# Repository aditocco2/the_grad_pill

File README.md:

# Overblinking: The LED Matrix Graduation Cap

A DIY graduation cap project that shows a slideshow of pictures, GIFs, videos, and scrolling text messages on a 64x64 LED matrix.

Includes a high-performance LED matrix driver, a custom 3D printed mounting system, and a custom PCB.

## Features
- Easy loading of data onto the SD card - no manual downscaling or image dumping needed
- SD card is exposed underneath the cap with a custom PCB, allowing easy replacement of cards
- Mode switch allows you to automatically switch to a less distracting "static mode" during speeches
- Whole system is powered through one battery pack
- Optional rain resistance using an acrylic sheet and 3D printed waterproofing shield
- Automatically initializes/recovers SD cards and survives card swaps
- Only required electronics skill for assembly is through-hole soldering

## Build Your Own
For instructions on how to make your own LED matrix graduation cap, read the full guide [here](https://overblinking.substack.com/guide)!

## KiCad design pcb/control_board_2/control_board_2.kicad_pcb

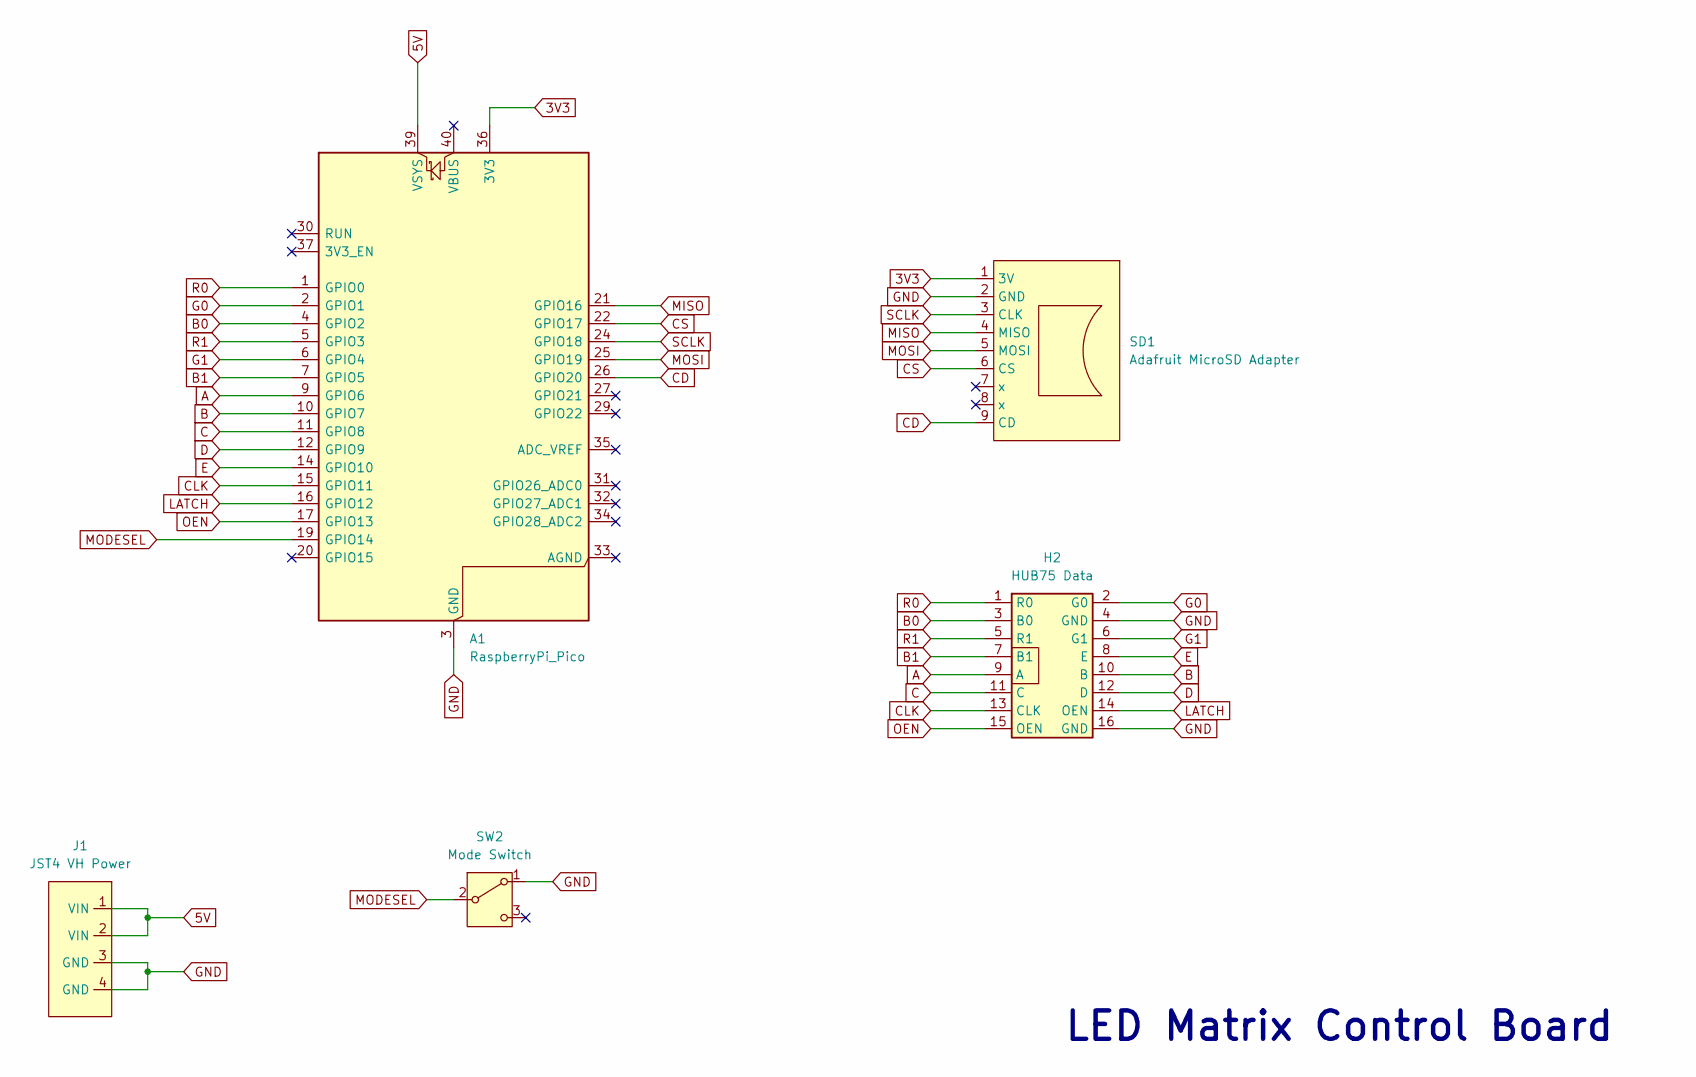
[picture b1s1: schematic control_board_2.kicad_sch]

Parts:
A1: RaspberryPi_Pico; RaspberryPi_Pico_Common_Unspecified
H2: HUB75 Data; IDC-Header_2x08_P2.54mm_Vertical
J1: JST4 VH Power; JST_VH_B4PS-VH_1x04_P3.96mm_Horizontal
SD1: Adafruit MicroSD Adapter; usd_breakout_adafruit
SW2: Mode Switch; SW_Slide-03_Wuerth-WS-SLTV_10x2.5x6.4_P2.54mm

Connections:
3V3: A1.36 (3V3), SD1.1 (3V)
5V: A1.39 (VSYS), J1.1 (VIN), J1.2 (VIN)
A: A1.9 (GPIO6), H2.9 (A)
B: A1.10 (GPIO7), H2.10 (B)
B0: A1.4 (GPIO2), H2.3 (B0)
B1: A1.7 (GPIO5), H2.7 (B1)
C: A1.11 (GPIO8), H2.11 (C)
CD: A1.26 (GPIO20), SD1.9 (CD)
CLK: A1.15 (GPIO11), H2.13 (CLK)
CS: A1.22 (GPIO17), SD1.6 (CS)
D: A1.12 (GPIO9), H2.12 (D)
E: A1.14 (GPIO10), H2.8 (E)
G0: A1.2 (GPIO1), H2.2 (G0)
G1: A1.6 (GPIO4), H2.6 (G1)
GND: A1.3 (GND), A1.8 (GND), A1.13 (GND), A1.18 (GND), A1.23 (GND), A1.28 (GND), A1.38 (GND), H2.4 (GND), H2.16 (GND), J1.3 (GND), J1.4 (GND), SD1.2 (GND), SW2.1 (A)
LATCH: A1.16 (GPIO12), H2.14 (OEN)
MISO: A1.21 (GPIO16), SD1.4 (MISO)
MODESEL: A1.19 (GPIO14), SW2.2 (B)
MOSI: A1.25 (GPIO19), SD1.5 (MOSI)
OEN: A1.17 (GPIO13), H2.15 (OEN)
R0: A1.1 (GPIO0), H2.1 (R0)
R1: A1.5 (GPIO3), H2.5 (R1)
SCLK: A1.24 (GPIO18), SD1.3 (CLK)

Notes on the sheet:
LED Matrix Control Board

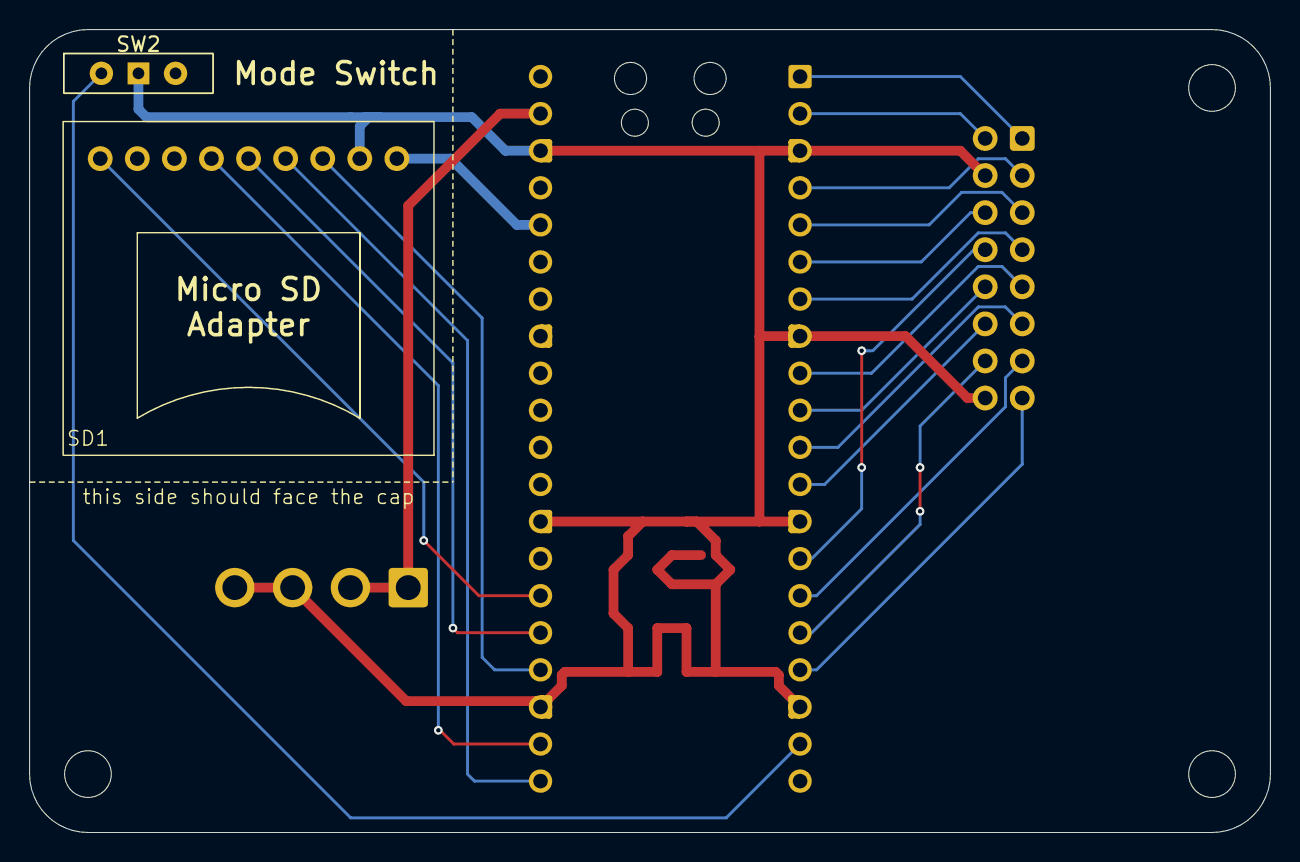
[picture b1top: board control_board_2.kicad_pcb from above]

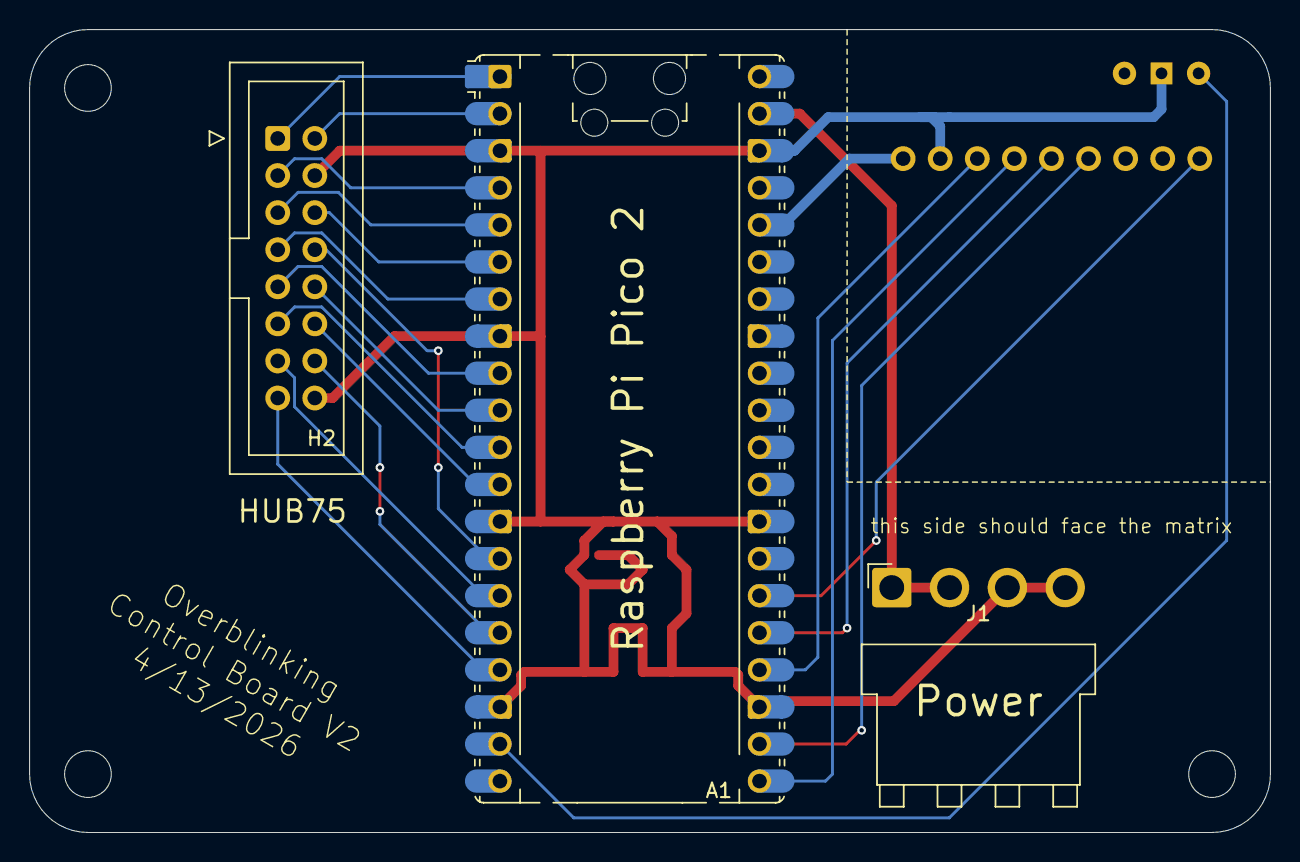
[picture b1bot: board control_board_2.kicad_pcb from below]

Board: 2 copper layers, 85.0 x 55.0 mm, 5 parts (3 on the bottom side), 23 nets.

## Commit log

2026-02-03 separated example hub75 code into functions
2026-02-10 organized files and made an easier cmake file
2026-02-13 It can play a video off the SD card now
    I have made great strides in lightslop technology today
2026-02-17 modified hub75 driver to use dma and have two buffers
2026-02-17 flicker fixed. sd card recovery still iffy
2026-02-17 made hub75 driver more secure
2026-02-18 Made SD Init non blocking with FSM! And some other things I guess
2026-02-21 made SD SPI not blocking with DMA, is it worth it?
    this was last night
2026-02-24 CPU-Free Refresh
2026-02-25 Still going
    hub75 driver separation complete, could use some more testing for smaller resolution compatibility
2026-03-14 FreeRTOS does not need to be here lol
2026-03-14 HUB75 MULTICORE and some SD cleanup
2026-03-21 Somewhat organized project
2026-03-21 JLCPCB has violated me
2026-03-24 made the python half of static mode. that's all i feel like doing tn
    im a lazy chud
2026-03-24 these interlocking fsms be tricky lowk
2026-04-14 control board 2 with switch
2026-04-25 oops
2026-04-26 ehh temporary revert
2026-04-27 made a scrolling text test file. no idea if it works
2026-04-28 Added PCB holes to mounting sheet
    Also organized some of the files
2026-04-28 oops forgot to center it
2026-04-30 scrolling text
2026-05-03 built the final cap. had to make waterproofing shield better
2026-05-05 added a check to ensure the card was actually flashed with data
    also renamed image_proc to file_proc, as text files are not exactly images
2026-05-06 Finally give it a proper readme
2026-05-13 increased max media for c program, added webp support, added os.walk finding
